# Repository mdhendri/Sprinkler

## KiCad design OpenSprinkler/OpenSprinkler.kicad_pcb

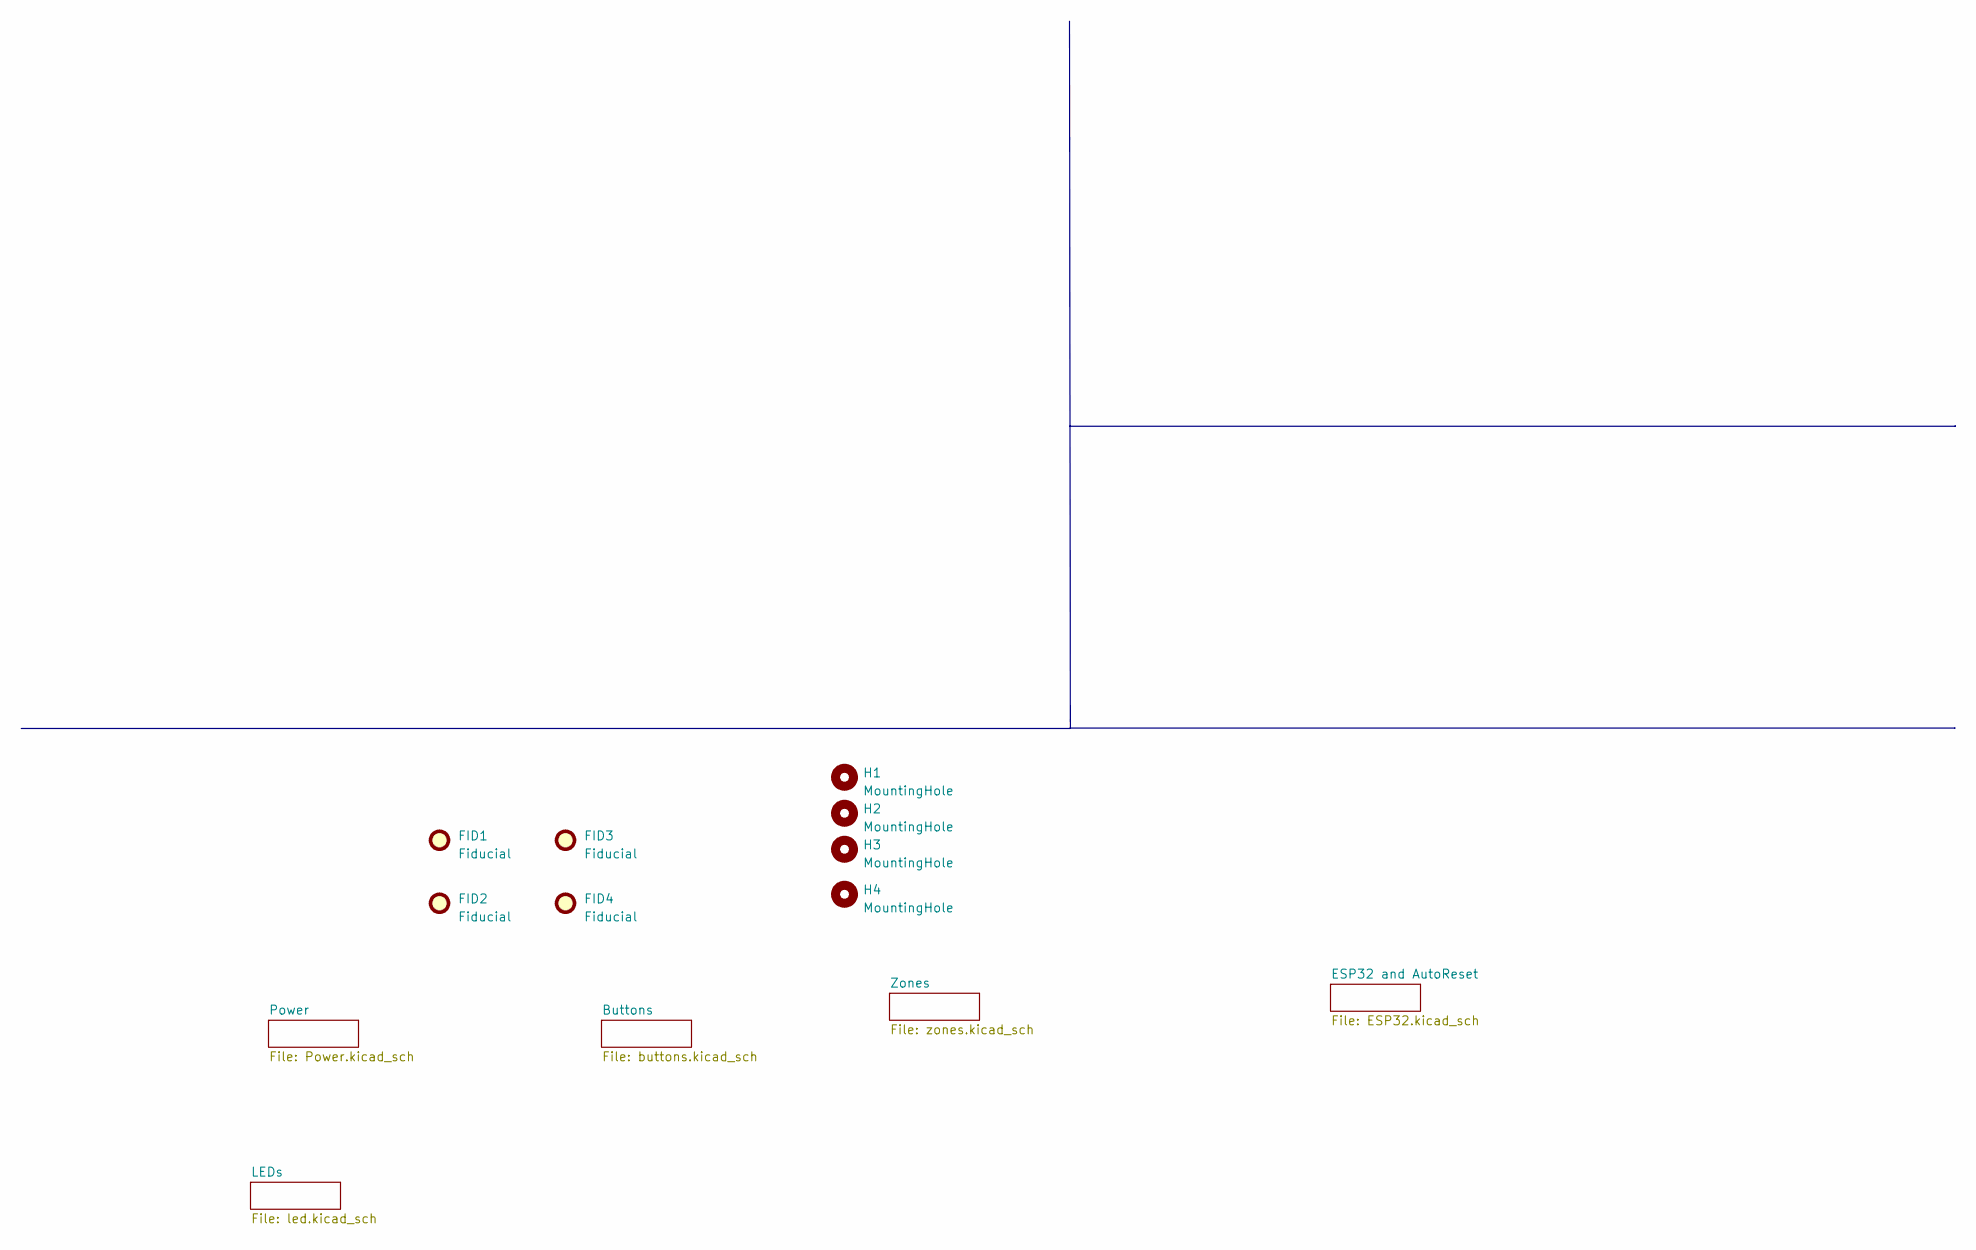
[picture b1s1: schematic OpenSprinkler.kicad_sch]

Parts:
FID1, FID2, FID3, FID4: Fiducial; Fiducial_0.5mm_Mask1.5mm
H1, H2, H3, H4: MountingHole; MountingHole_2.7mm

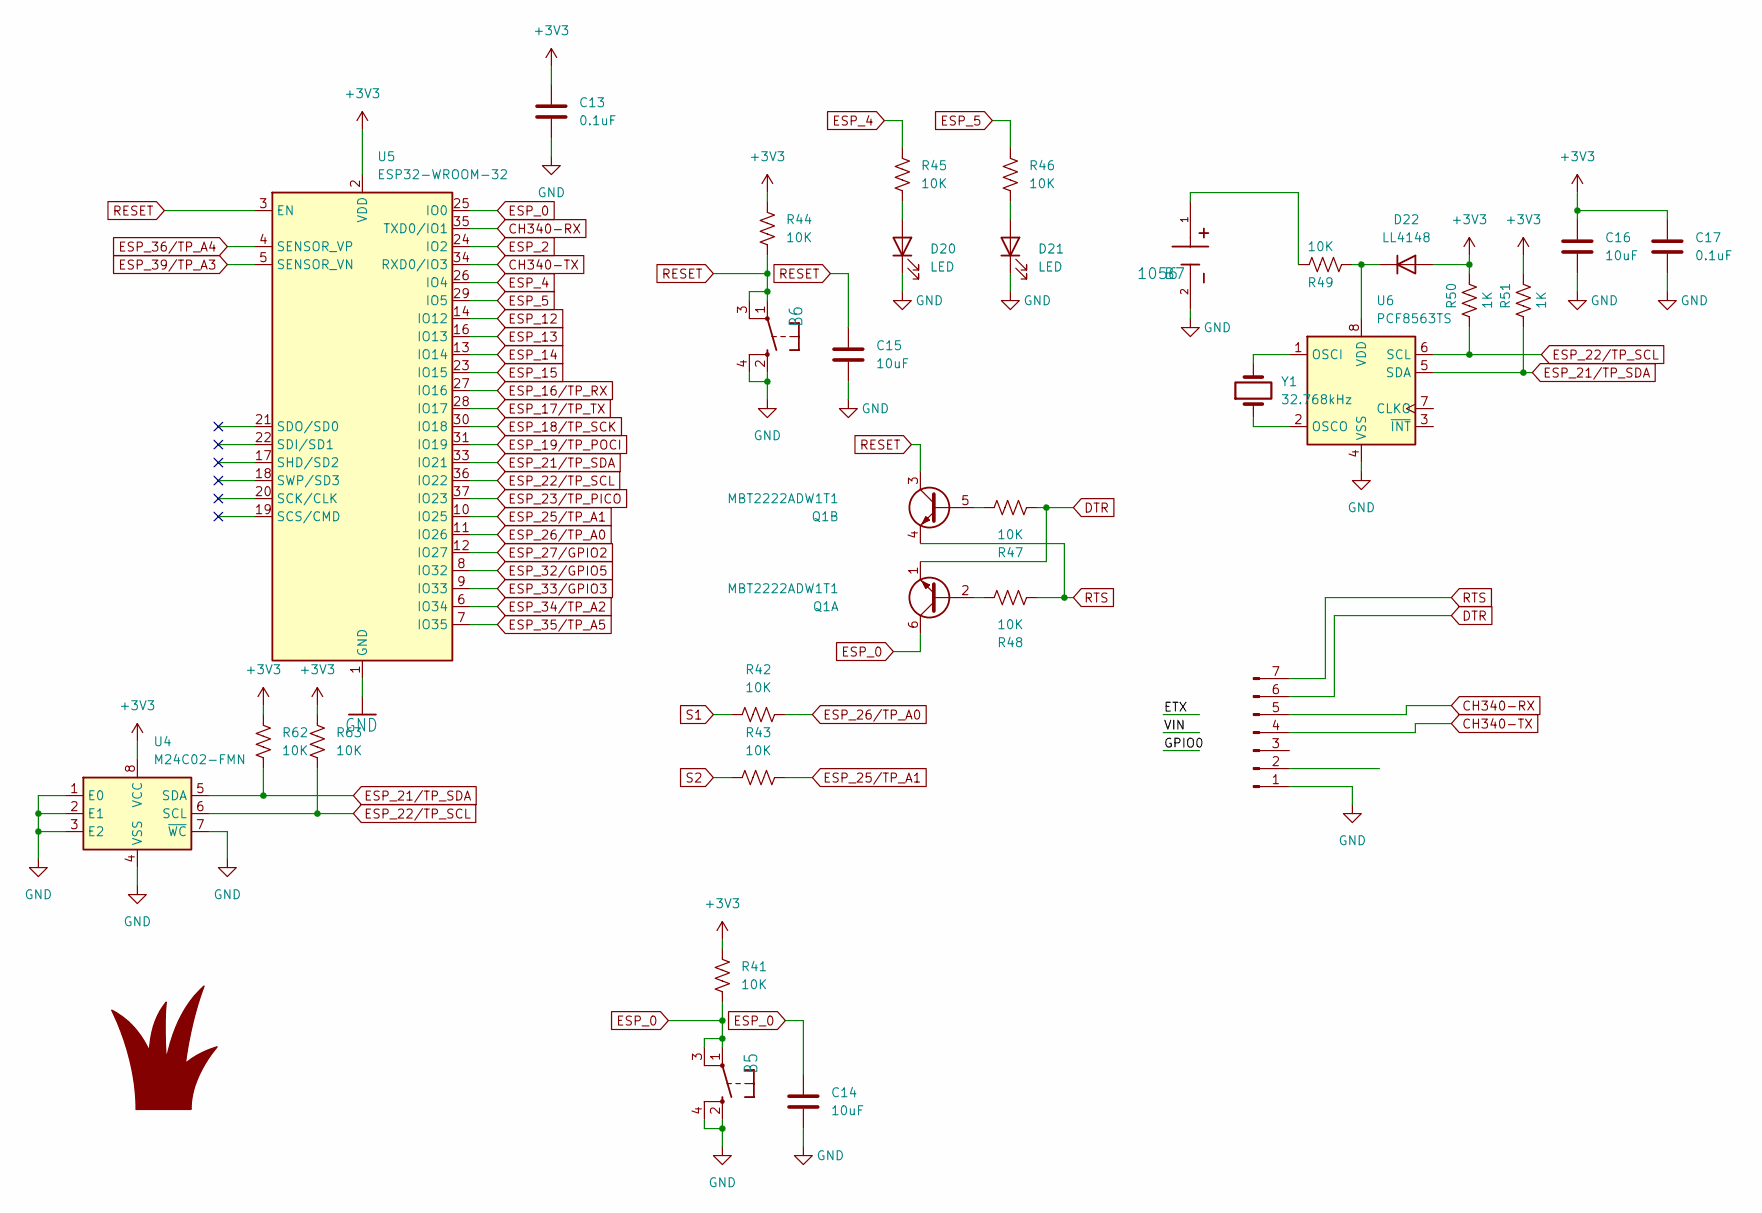
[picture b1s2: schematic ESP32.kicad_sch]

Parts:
B5, B6: SPST_TACTEVQQ2; SW_SPST_EVQQ2
B7: 1056; 1048P_KEY; PARTREV C
C13, C17: 0.1uF; C_0603_1608Metric_Pad1.08x0.95mm_HandSolder
C14, C15, C16: 10uF; C_0603_1608Metric_Pad1.08x0.95mm_HandSolder
D20, D21: LED; LED_0603_1608Metric_Pad1.05x0.95mm_HandSolder
D22: LL4148; D_MiniMELF
Q1: MBT2222ADW1T1; SOT-363_SC-70-6
R41, R42, R43, R44, R45, R46, R47, R48, R49, R62, R63: 10K; R_0603_1608Metric_Pad0.98x0.95mm_HandSolder
R50, R51: 1K; R_0603_1608Metric_Pad0.98x0.95mm_HandSolder
U4: M24C02-FMN; SOIC-8_3.9x4.9mm_P1.27mm
U5: ESP32-WROOM-32
U6: PCF8563TS; MSOP-8_3x3mm_P0.65mm
U$1: GOLDFINGER_2X3; PinHeader_1x07_P2.54mm_Vertical
Y1: 32.768kHz; XTAL_ECS-31B_ECS

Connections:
+3V3: C13.1, C16.1, C17.1, D22.2 (A), R41.1, R44.1, R50.1, R51.1, R62.1, R63.1, U4.8 (VCC), U5.2 (VDD); also elsewhere on the board
CH340-RX: U5.35 (TXD0/IO1), U$1.5
CH340-TX: U5.34 (RXD0/IO3), U$1.4
DTR: Q1.1 (E1), R47.1, U$1.6
ESP_0: B5.1, B5.3, C14.1, Q1.6 (C1), R41.2, U5.25 (IO0)
ESP_2: U5.24 (IO2)
ESP_4: R45.1, U5.26 (IO4)
ESP_5: R46.1, U5.29 (IO5)
ESP_12: U5.14 (IO12); also elsewhere on the board
ESP_13: U5.16 (IO13); also elsewhere on the board
ESP_14: U5.13 (IO14); also elsewhere on the board
ESP_15: U5.23 (IO15); also elsewhere on the board
ESP_16/TP_RX: U5.27 (IO16)
ESP_17/TP_TX: U5.28 (IO17)
ESP_18/TP_SCK: U5.30 (IO18)
ESP_19/TP_POCI: U5.31 (IO19)
ESP_21/TP_SDA: R51.2, R62.2, U4.5 (SDA), U5.33 (IO21), U6.5 (SDA); also elsewhere on the board
ESP_22/TP_SCL: R50.2, R63.2, U4.6 (SCL), U5.36 (IO22), U6.6 (SCL); also elsewhere on the board
ESP_23/TP_PICO: U5.37 (IO23)
ESP_25/TP_A1: R43.2, U5.10 (IO25)
ESP_26/TP_A0: R42.2, U5.11 (IO26)
ESP_27/GPIO2: U5.12 (IO27); also elsewhere on the board
ESP_32/GPIO5: U5.8 (IO32)
ESP_33/GPIO3: U5.9 (IO33)
ESP_34/TP_A2: U5.6 (IO34); also elsewhere on the board
ESP_35/TP_A5: U5.7 (IO35)
ESP_36/TP_A4: U5.4 (SENSOR_VP)
ESP_39/TP_A3: U5.5 (SENSOR_VN)
GND: B5.2, B5.4, B6.2, B6.4, B7.2, C13.2, C14.2, C15.2, C16.2, C17.2, D20.1 (K), D21.1 (K), U4.1 (E0), U4.2 (E1), U4.3 (E2), U4.4 (VSS), U4.7 (~WC), U5.1 (GND), U5.15 (GND), U5.38 (GND), U5.39 (GND), U6.4 (VSS), U$1.1; also elsewhere on the board
unnamed: B7.1, R49.1
unnamed: D20.2 (A), R45.2
unnamed: D21.2 (A), R46.2
unnamed: D22.1 (K), R49.2, U6.8 (VDD)
unnamed: Q1.2 (B1), R48.2
unnamed: Q1.5 (B2), R47.2
unnamed: U6.1 (OSCI), Y1.2
unnamed: U6.2 (OSCO), Y1.1
RESET: B6.1, B6.3, C15.1, Q1.3 (C2), R44.2, U5.3 (EN)
RTS: Q1.4 (E2), R48.1, U$1.7
S1: R42.1; also elsewhere on the board
S2: R43.1; also elsewhere on the board

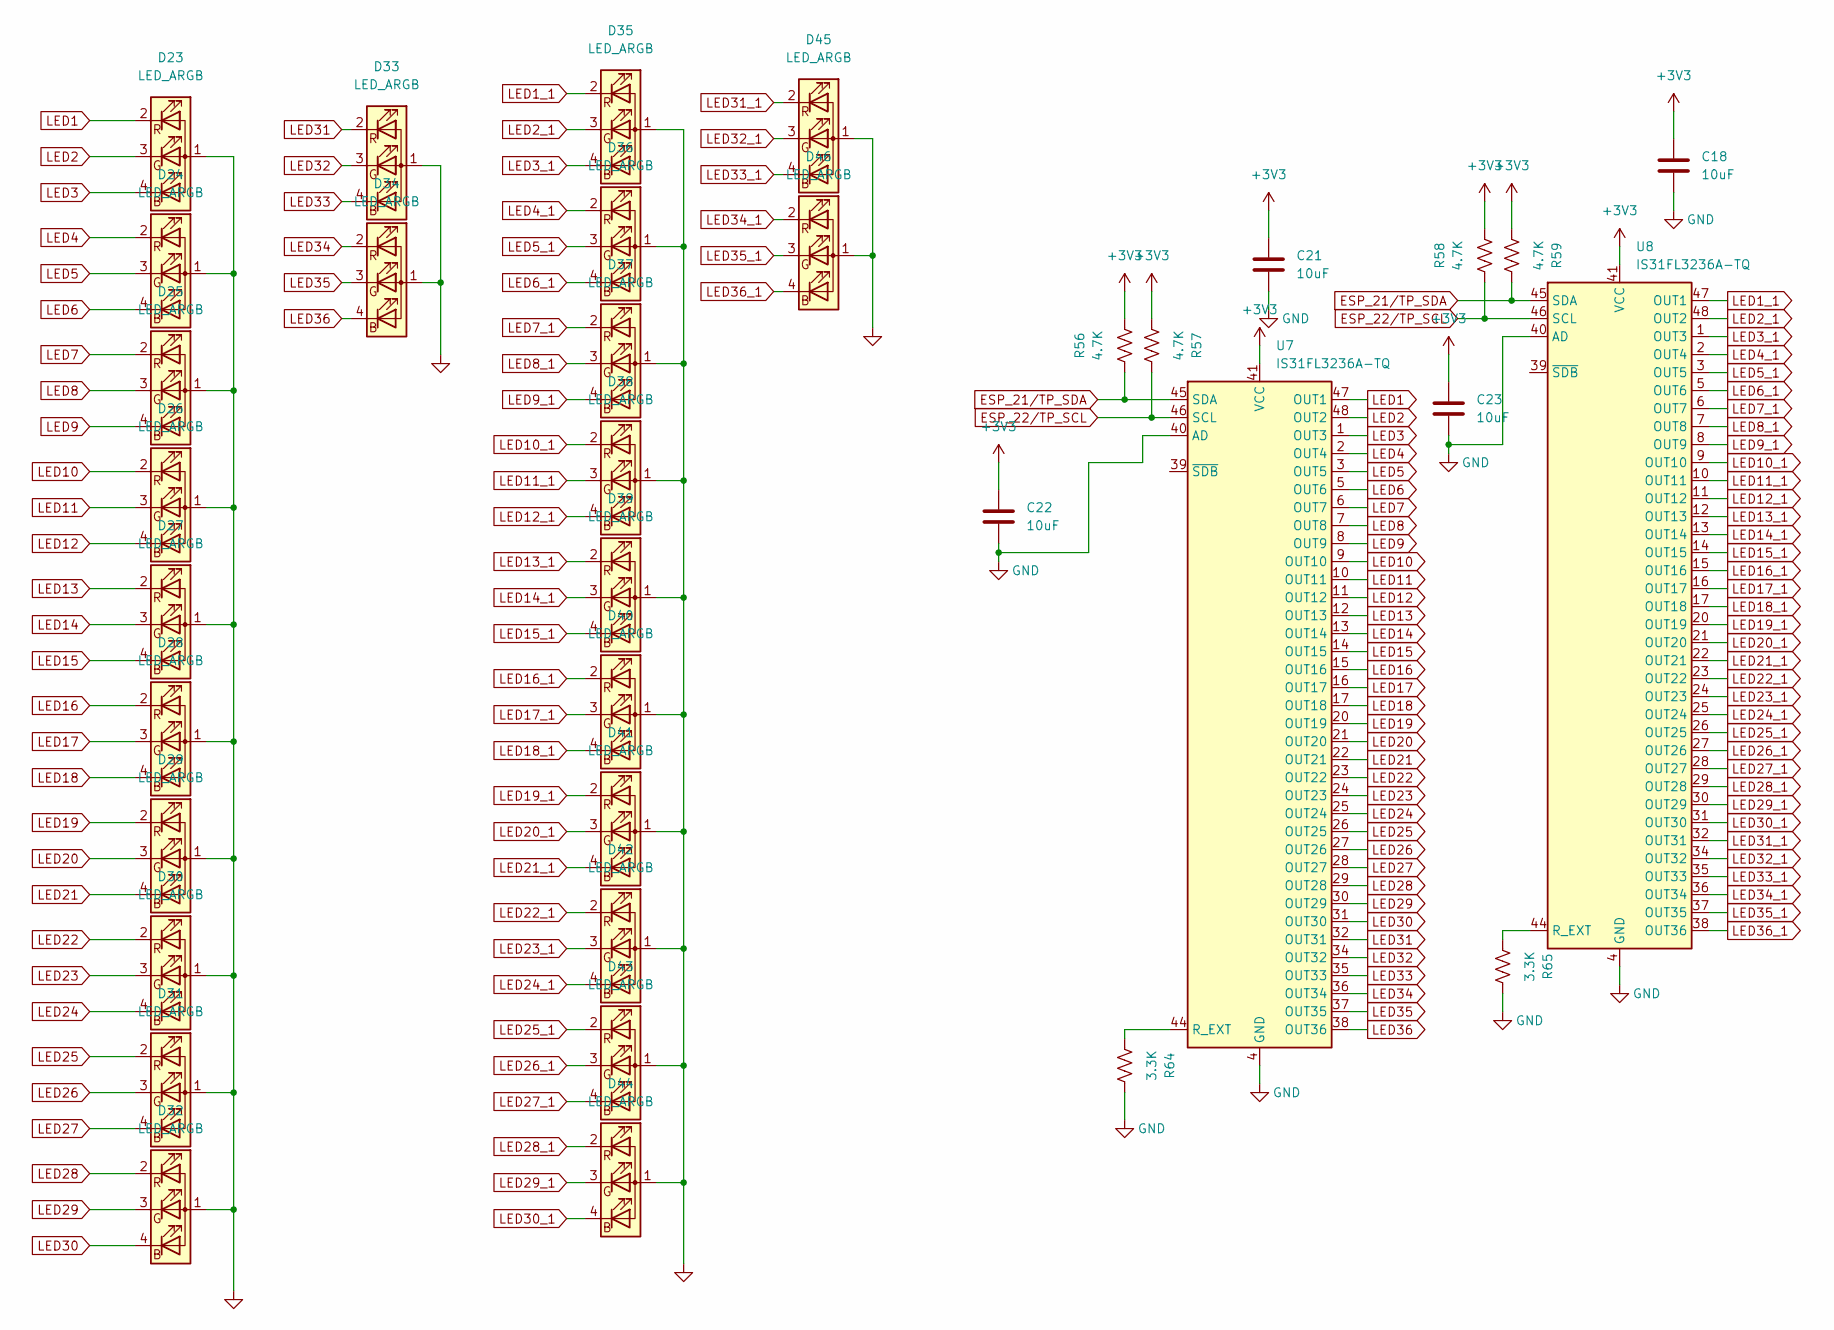
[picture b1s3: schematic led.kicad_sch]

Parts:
C18, C21, C22, C23: 10uF; C_0603_1608Metric_Pad1.08x0.95mm_HandSolder
D23, D24, D25, D26, D27, D28, D29, D30, D31, D32, D33, D34, D35, D36, D37, D38, D39, D40, D41, D42, D43, D44, D45, D46: LED_ARGB; LED_EASR3212RGBA0
R56, R57, R58, R59: 4.7K; R_0603_1608Metric_Pad0.98x0.95mm_HandSolder
R64, R65: 3.3K; R_0603_1608Metric_Pad0.98x0.95mm_HandSolder
U7, U8: IS31FL3236A-TQ; TQFP-48-1EP_7x7mm_P0.5mm_EP4.11x4.11mm

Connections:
+3V3: C18.1, C21.1, C22.1, C23.1, R56.2, R57.1, R58.2, R59.1, U7.41 (VCC), U8.41 (VCC); also elsewhere on the board
ESP_21/TP_SDA: R56.1, R59.2, U7.45 (SDA), U8.45 (SDA); also elsewhere on the board
ESP_22/TP_SCL: R57.2, R58.1, U7.46 (SCL), U8.46 (SCL); also elsewhere on the board
GND: C18.2, C21.2, C22.2, C23.2, D23.1 (A), D24.1 (A), D25.1 (A), D26.1 (A), D27.1 (A), D28.1 (A), D29.1 (A), D30.1 (A), D31.1 (A), D32.1 (A), D33.1 (A), D34.1 (A), D35.1 (A), D36.1 (A), D37.1 (A), D38.1 (A), D39.1 (A), D40.1 (A), D41.1 (A), D42.1 (A), D43.1 (A), D44.1 (A), D45.1 (A), D46.1 (A), R64.2, R65.2, U7.4 (GND), U7.18 (GND), U7.19 (GND), U7.33 (GND), U7.40 (AD), U7.42 (GND), U7.43 (GND), U7.49 (GND), U8.4 (GND), U8.18 (GND), U8.19 (GND), U8.33 (GND), U8.40 (AD), U8.42 (GND), U8.43 (GND), U8.49 (GND); also elsewhere on the board
LED1: D23.2 (RK), U7.47 (OUT1)
LED1_1: D35.2 (RK), U8.47 (OUT1)
LED2: D23.3 (GK), U7.48 (OUT2)
LED2_1: D35.3 (GK), U8.48 (OUT2)
LED3: D23.4 (BK), U7.1 (OUT3)
LED3_1: D35.4 (BK), U8.1 (OUT3)
LED4: D24.2 (RK), U7.2 (OUT4)
LED4_1: D36.2 (RK), U8.2 (OUT4)
LED5: D24.3 (GK), U7.3 (OUT5)
LED5_1: D36.3 (GK), U8.3 (OUT5)
LED6: D24.4 (BK), U7.5 (OUT6)
LED6_1: D36.4 (BK), U8.5 (OUT6)
LED7: D25.2 (RK), U7.6 (OUT7)
LED7_1: D37.2 (RK), U8.6 (OUT7)
LED8: D25.3 (GK), U7.7 (OUT8)
LED8_1: D37.3 (GK), U8.7 (OUT8)
LED9: D25.4 (BK), U7.8 (OUT9)
LED9_1: D37.4 (BK), U8.8 (OUT9)
LED10: D26.2 (RK), U7.9 (OUT10)
LED10_1: D38.2 (RK), U8.9 (OUT10)
LED11: D26.3 (GK), U7.10 (OUT11)
LED11_1: D38.3 (GK), U8.10 (OUT11)
LED12: D26.4 (BK), U7.11 (OUT12)
LED12_1: D38.4 (BK), U8.11 (OUT12)
LED13: D27.2 (RK), U7.12 (OUT13)
LED13_1: D39.2 (RK), U8.12 (OUT13)
LED14: D27.3 (GK), U7.13 (OUT14)
LED14_1: D39.3 (GK), U8.13 (OUT14)
LED15: D27.4 (BK), U7.14 (OUT15)
LED15_1: D39.4 (BK), U8.14 (OUT15)
LED16: D28.2 (RK), U7.15 (OUT16)
LED16_1: D40.2 (RK), U8.15 (OUT16)
LED17: D28.3 (GK), U7.16 (OUT17)
LED17_1: D40.3 (GK), U8.16 (OUT17)
LED18: D28.4 (BK), U7.17 (OUT18)
LED18_1: D40.4 (BK), U8.17 (OUT18)
LED19: D29.2 (RK), U7.20 (OUT19)
LED19_1: D41.2 (RK), U8.20 (OUT19)
LED20: D29.3 (GK), U7.21 (OUT20)
LED20_1: D41.3 (GK), U8.21 (OUT20)
LED21: D29.4 (BK), U7.22 (OUT21)
LED21_1: D41.4 (BK), U8.22 (OUT21)
LED22: D30.2 (RK), U7.23 (OUT22)
LED22_1: D42.2 (RK), U8.23 (OUT22)
LED23: D30.3 (GK), U7.24 (OUT23)
LED23_1: D42.3 (GK), U8.24 (OUT23)
LED24: D30.4 (BK), U7.25 (OUT24)
LED24_1: D42.4 (BK), U8.25 (OUT24)
LED25: D31.2 (RK), U7.26 (OUT25)
LED25_1: D43.2 (RK), U8.26 (OUT25)
LED26: D31.3 (GK), U7.27 (OUT26)
LED26_1: D43.3 (GK), U8.27 (OUT26)
LED27: D31.4 (BK), U7.28 (OUT27)
LED27_1: D43.4 (BK), U8.28 (OUT27)
LED28: D32.2 (RK), U7.29 (OUT28)
LED28_1: D44.2 (RK), U8.29 (OUT28)
LED29: D32.3 (GK), U7.30 (OUT29)
LED29_1: D44.3 (GK), U8.30 (OUT29)
LED30: D32.4 (BK), U7.31 (OUT30)
LED30_1: D44.4 (BK), U8.31 (OUT30)
LED31: D33.2 (RK), U7.32 (OUT31)
LED31_1: D45.2 (RK), U8.32 (OUT31)
LED32: D33.3 (GK), U7.34 (OUT32)
LED32_1: D45.3 (GK), U8.34 (OUT32)
LED33: D33.4 (BK), U7.35 (OUT33)
LED33_1: D45.4 (BK), U8.35 (OUT33)
LED34: D34.2 (RK), U7.36 (OUT34)
LED34_1: D46.2 (RK), U8.36 (OUT34)
LED35: D34.3 (GK), U7.37 (OUT35)
LED35_1: D46.3 (GK), U8.37 (OUT35)
LED36: D34.4 (BK), U7.38 (OUT36)
LED36_1: D46.4 (BK), U8.38 (OUT36)
unnamed: R64.1, U7.44 (R_EXT)
unnamed: R65.1, U8.44 (R_EXT)

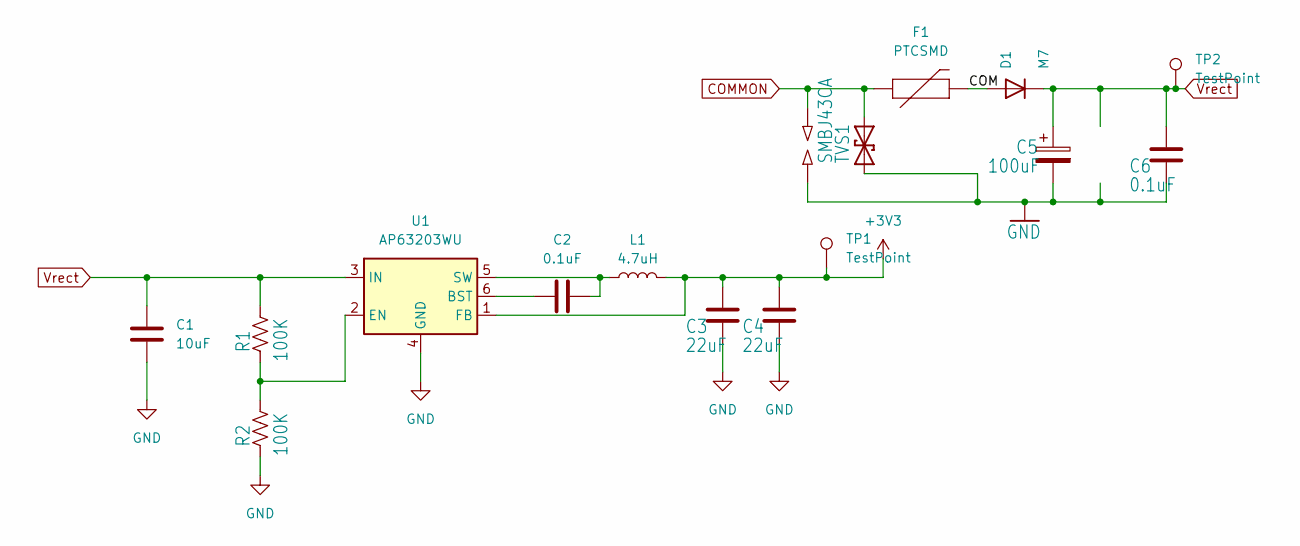
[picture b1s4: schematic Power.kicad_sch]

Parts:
C1: 10uF; C_1210_3225Metric_Pad1.33x2.70mm_HandSolder
C2: 0.1uF; C_0805_2012Metric_Pad1.18x1.45mm_HandSolder
C3, C4: 22uF; C_0805_2012Metric_Pad1.18x1.45mm_HandSolder
C5: 100uF; C_Elec_8x10.2
C6: 0.1uF; C_1206_3216Metric_Pad1.33x1.80mm_HandSolder
D1: M7; D_SMA
F1: PTCSMD; Fuse_Bourns_MF-SM_7.98x5.44mm
L1: 4.7uH; L_Abracon_ASPI-0425
R1, R2: 100K; R_0603_1608Metric_Pad0.98x0.95mm_HandSolder
SP1: PCB-SGAP; Sparkgap
TP1, TP2: TestPoint; TestPoint_Pad_D1.0mm
TVS1: SMBJ43CA; SMBJSeries_LTF
U1: AP63203WU; TSOT-23-6

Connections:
+3V3: C3.1, C4.1, L1.2, TP1.1, U1.1 (FB); also elsewhere on the board
/Power/COM: D1.2 (A), F1.2
COMMON: F1.1, SP1.2, TVS1.2 (C); also elsewhere on the board
GND: C1.2, C3.2, C4.2, C5.2, C6.2, R2.1, SP1.1, TVS1.1 (A), U1.4 (GND); also elsewhere on the board
unnamed: C2.1, U1.6 (BST)
unnamed: R1.1, R2.2, U1.2 (EN)
unnamed: C2.2, L1.1, U1.5 (SW)
Vrect: C1.1, C5.1, C6.1, D1.1 (K), R1.2, TP2.1, U1.3 (IN)

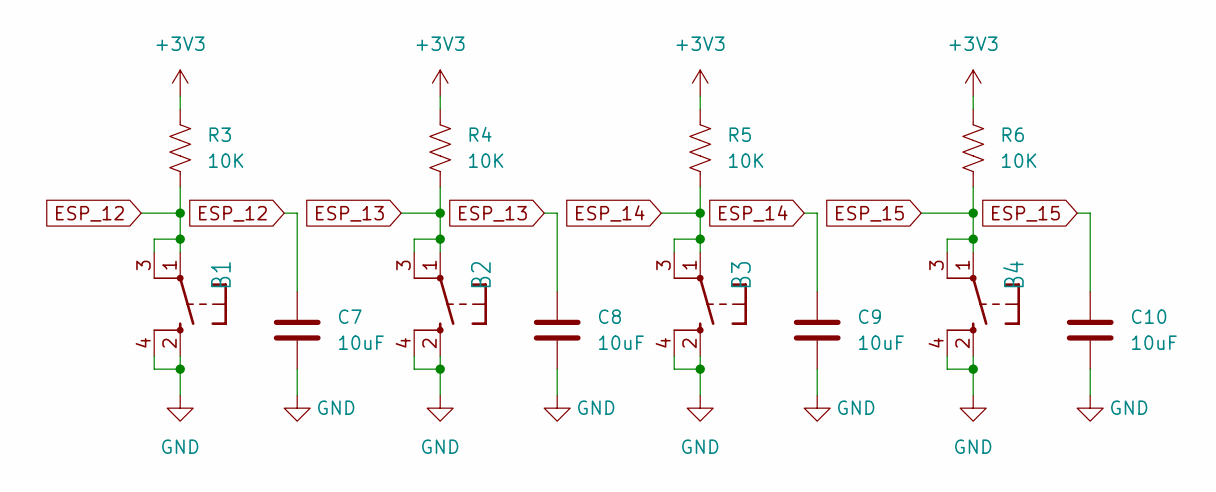
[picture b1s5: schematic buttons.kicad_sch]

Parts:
B1, B2, B3, B4: SPST_TACTEVQQ2; SW_SPST_EVQQ2
C7, C8, C9, C10: 10uF; C_0603_1608Metric_Pad1.08x0.95mm_HandSolder
R3, R4, R5, R6: 10K; R_0603_1608Metric_Pad0.98x0.95mm_HandSolder

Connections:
+3V3: R3.1, R4.1, R5.1, R6.1; also elsewhere on the board
ESP_12: B1.1, B1.3, C7.1, R3.2; also elsewhere on the board
ESP_13: B2.1, B2.3, C8.1, R4.2; also elsewhere on the board
ESP_14: B3.1, B3.3, C9.1, R5.2; also elsewhere on the board
ESP_15: B4.1, B4.3, C10.1, R6.2; also elsewhere on the board
GND: B1.2, B1.4, B2.2, B2.4, B3.2, B3.4, B4.2, B4.4, C7.2, C8.2, C9.2, C10.2; also elsewhere on the board

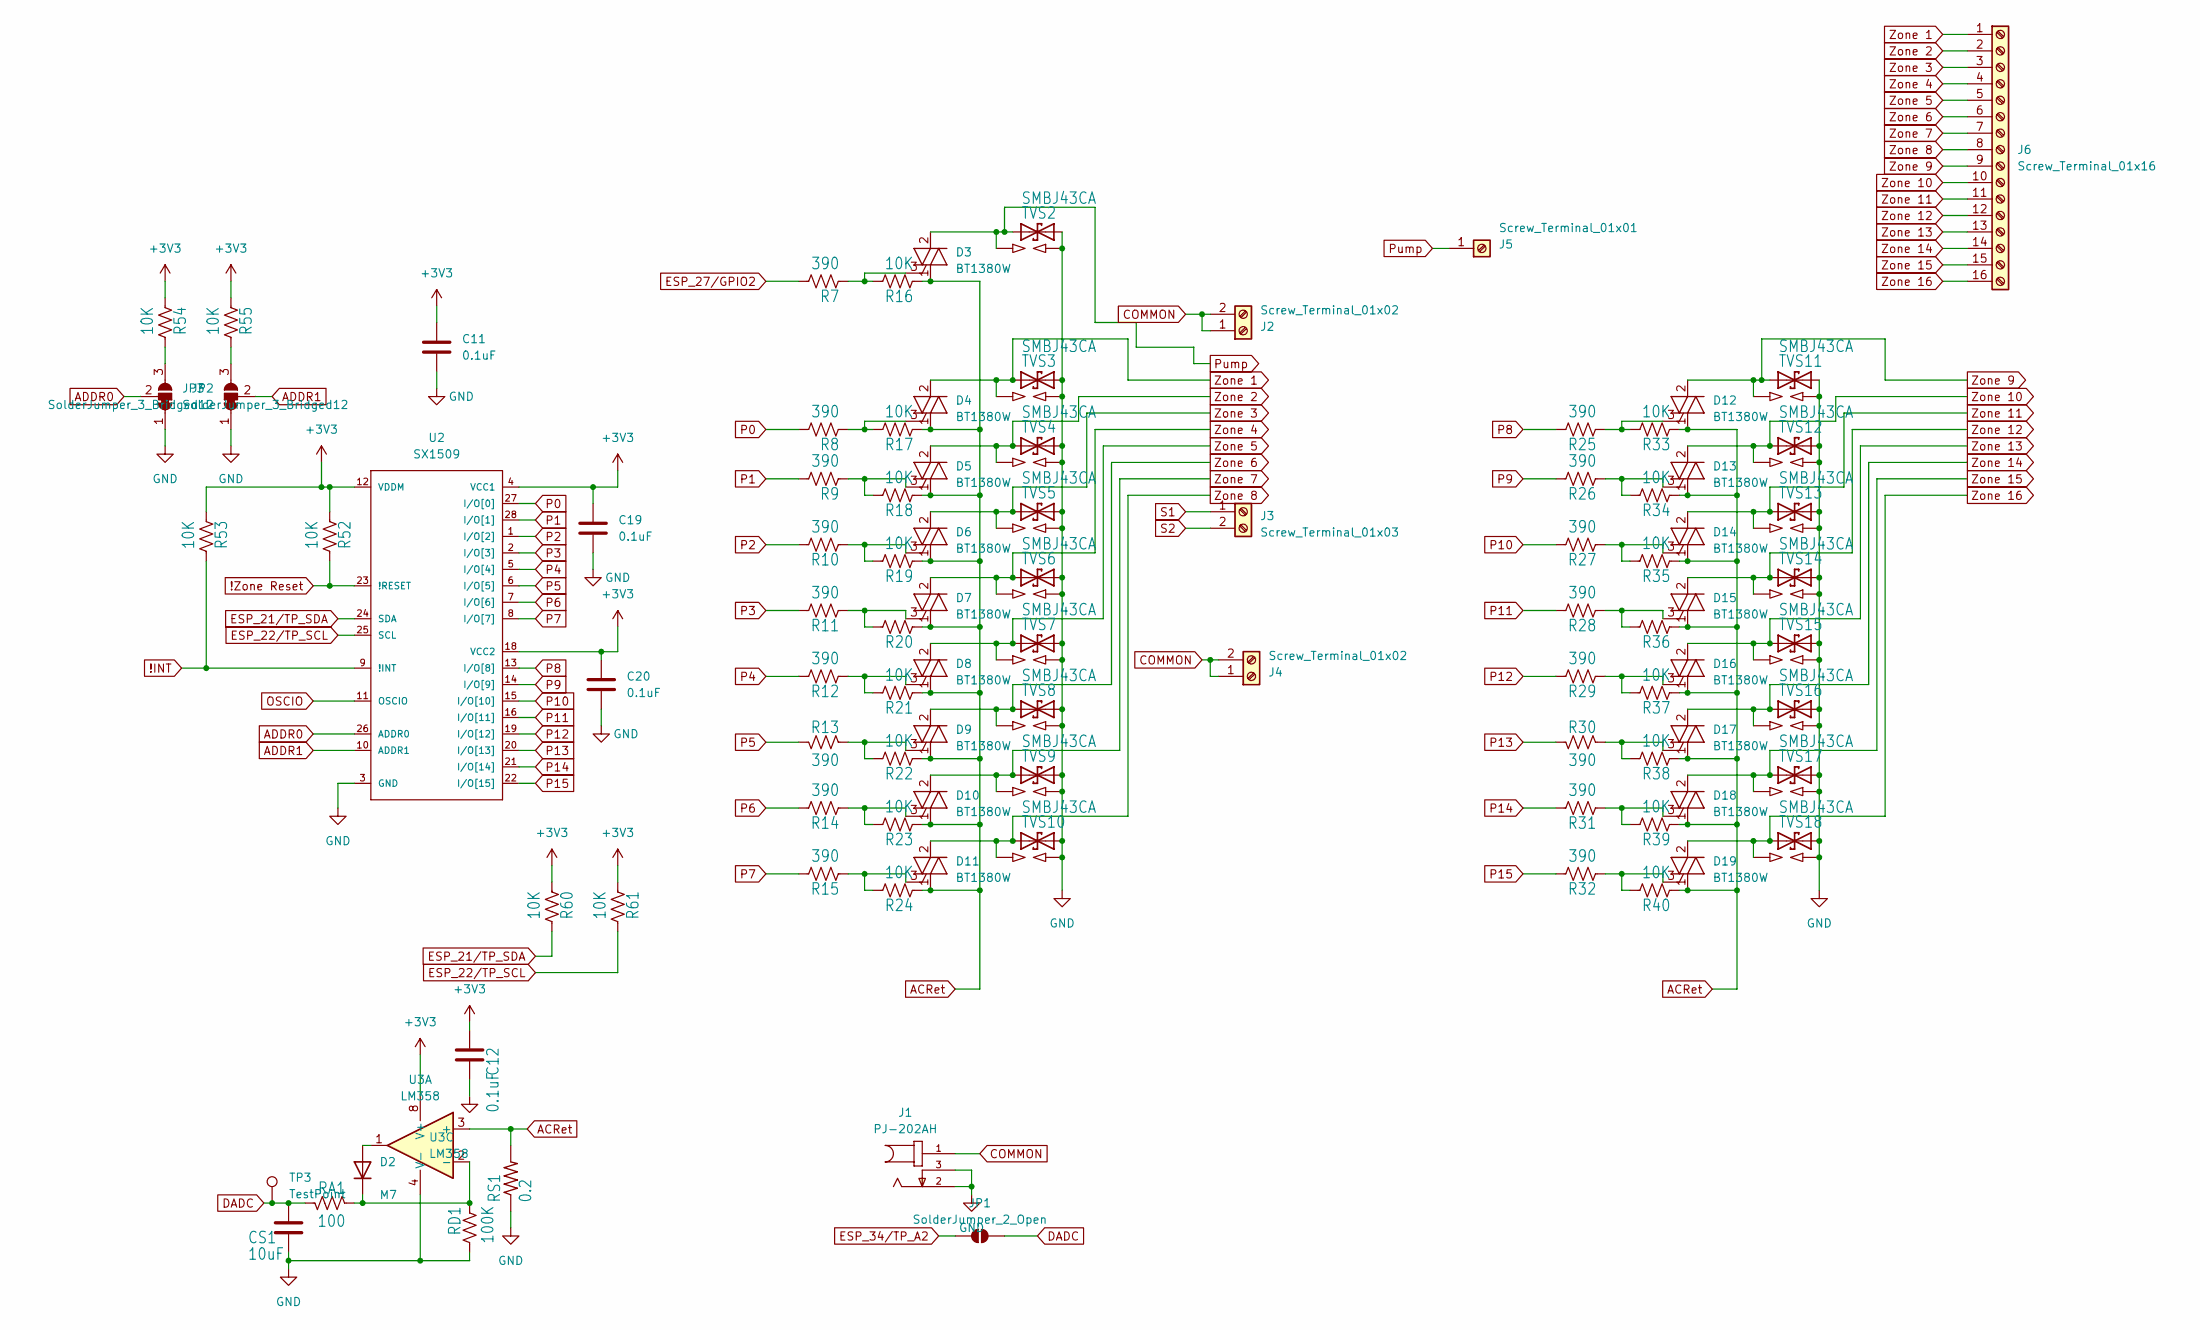
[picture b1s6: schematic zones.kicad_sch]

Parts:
C11, C12, C19, C20: 0.1uF; C_0603_1608Metric_Pad1.08x0.95mm_HandSolder
CS1: 10uF; C_0603_1608Metric_Pad1.08x0.95mm_HandSolder
D2: M7; D_SMA
D3, D4, D5, D6, D7, D8, D9, D10, D11, D12, D13, D14, D15, D16, D17, D18, D19: BT1380W; SOT-223
J1: PJ-202AH; BarrelJack_Kycon_KLDX-0202-xC_Horizontal; PART_REV 1.02
J2, J4: Screw_Terminal_01x02; TerminalBlock_WAGO_236-502_1x02_P7.50mm_45Degree
J3: Screw_Terminal_01x03; TerminalBlock_WAGO_236-502_1x02_P7.50mm_45Degree
J5: Screw_Terminal_01x01; TerminalBlock_WAGO_236-501_1x01_P7.50mm_45Degree
J6: Screw_Terminal_01x16; TerminalBlock_WAGO_236-516_1x16_P7.50mm_45Degree
JP1: SolderJumper_2_Open; SolderJumper-2_P1.3mm_Open_Pad1.0x1.5mm
JP2, JP3: SolderJumper_3_Bridged12; SolderJumper-3_P1.3mm_Bridged2Bar12_Pad1.0x1.5mm
R7, R8, R9, R10, R11, R12, R13, R14, R15, R25, R26, R27, R28, R29, R30, R31, R32: 390; R_0603_1608Metric_Pad0.98x0.95mm_HandSolder
R16, R17, R18, R19, R20, R21, R22, R23, R24, R33, R34, R35, R36, R37, R38, R39, R40, R52, R53, R54, R55, R60, R61: 10K; R_0603_1608Metric_Pad0.98x0.95mm_HandSolder
RA1: 100; R_0603_1608Metric_Pad0.98x0.95mm_HandSolder
RD1: 100K; R_0603_1608Metric_Pad0.98x0.95mm_HandSolder
RS1: 0.2; R_1206_3216Metric_Pad1.30x1.75mm_HandSolder
SP2, SP3, SP4, SP5, SP6, SP7, SP8, SP9, SP10, SP11, SP12, SP13, SP14, SP15, SP16, SP17, SP18: PCB-SGAP; Sparkgap
TP3: TestPoint; TestPoint_Pad_D1.0mm
TVS2, TVS3, TVS4, TVS5, TVS6, TVS7, TVS8, TVS9, TVS10, TVS11, TVS12, TVS13, TVS14, TVS15, TVS16, TVS17, TVS18: SMBJ43CA; D_SMB
U2: SX1509; QFN40P400X400X60-29N
U3: LM358; SOIC-8_3.9x4.9mm_P1.27mm

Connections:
!INT: R53.2, U2.9 (!INT)
!Zone Reset: R52.2, U2.23 (!RESET)
+3V3: C11.1, C12.1, C19.1, C20.1, R52.1, R53.1, R54.1, R55.1, R60.1, R61.1, U2.4 (VCC1), U2.12 (VDDM), U2.18 (VCC2), U3.8 (V+); also elsewhere on the board
ACRet: D3.1 (A1), D4.1 (A1), D5.1 (A1), D6.1 (A1), D7.1 (A1), D8.1 (A1), D9.1 (A1), D10.1 (A1), D11.1 (A1), D12.1 (A1), D13.1 (A1), D14.1 (A1), D15.1 (A1), D16.1 (A1), D17.1 (A1), D18.1 (A1), D19.1 (A1), R16.1, R17.1, R18.1, R19.1, R20.1, R21.1, R22.1, R23.1, R24.1, R33.1, R34.1, R35.1, R36.1, R37.1, R38.1, R39.1, R40.1, RS1.2, U3.3 (+)
ADDR0: JP3.2 (C), U2.26 (ADDR0)
ADDR1: JP2.2 (C), U2.10 (ADDR1)
COMMON: J1.1, J2.1, J2.2, J4.1, J4.2; also elsewhere on the board
DADC: CS1.1, JP1.2 (B), RA1.2, TP3.1
ESP_21/TP_SDA: R60.2, U2.24 (SDA); also elsewhere on the board
ESP_22/TP_SCL: R61.2, U2.25 (SCL); also elsewhere on the board
ESP_27/GPIO2: R7.2; also elsewhere on the board
ESP_34/TP_A2: JP1.1 (A); also elsewhere on the board
GND: C11.2, C12.2, C19.2, C20.2, CS1.2, J1.2, J1.3, JP2.1 (A), JP3.1 (A), RD1.1, RS1.1, SP2.2, SP3.2, SP4.2, SP5.2, SP6.2, SP7.2, SP8.2, SP9.2, SP10.2, SP11.2, SP12.2, SP13.2, SP14.2, SP15.2, SP16.2, SP17.2, SP18.2, TVS2.2 (C), TVS3.2 (C), TVS4.2 (C), TVS5.2 (C), TVS6.2 (C), TVS7.2 (C), TVS8.2 (C), TVS9.2 (C), TVS10.2 (C), TVS11.2 (C), TVS12.2 (C), TVS13.2 (C), TVS14.2 (C), TVS15.2 (C), TVS16.2 (C), TVS17.2 (C), TVS18.2 (C), U2.3 (GND), U2.17 (GND), U2.29 (GND), U3.4 (V-); also elsewhere on the board
unnamed: D2.2 (A), U3.1
unnamed: D2.1 (K), RA1.1, RD1.2, U3.2 (-)
unnamed: D3.3 (G), R7.1, R16.2
unnamed: D4.3 (G), R8.1, R17.2
unnamed: D5.3 (G), R9.1, R18.2
unnamed: D6.3 (G), R10.1, R19.2
unnamed: D7.3 (G), R11.1, R20.2
unnamed: D8.3 (G), R12.1, R21.2
unnamed: D9.3 (G), R13.1, R22.2
unnamed: D10.3 (G), R14.1, R23.2
unnamed: D11.3 (G), R15.1, R24.2
unnamed: D12.3 (G), R25.1, R33.2
unnamed: D13.3 (G), R26.1, R34.2
unnamed: D14.3 (G), R27.1, R35.2
unnamed: D15.3 (G), R28.1, R36.2
unnamed: D16.3 (G), R29.1, R37.2
unnamed: D17.3 (G), R30.1, R38.2
unnamed: D18.3 (G), R31.1, R39.2
unnamed: D19.3 (G), R32.1, R40.2
unnamed: JP2.3 (B), R55.2
unnamed: JP3.3 (B), R54.2
OSCIO: U2.11 (OSCIO)
P0: R8.2, U2.27 (I/O[0])
P1: R9.2, U2.28 (I/O[1])
P2: R10.2, U2.1 (I/O[2])
P3: R11.2, U2.2 (I/O[3])
P4: R12.2, U2.5 (I/O[4])
P5: R13.2, U2.6 (I/O[5])
P6: R14.2, U2.7 (I/O[6])
P7: R15.2, U2.8 (I/O[7])
P8: R25.2, U2.13 (I/O[8])
P9: R26.2, U2.14 (I/O[9])
P10: R27.2, U2.15 (I/O[10])
P11: R28.2, U2.16 (I/O[11])
P12: R29.2, U2.19 (I/O[12])
P13: R30.2, U2.20 (I/O[13])
P14: R31.2, U2.21 (I/O[14])
P15: R32.2, U2.22 (I/O[15])
Pump: D3.2 (A2), D3.4 (A4), J5.1, SP2.1, TVS2.1 (A)
S1: J3.1; also elsewhere on the board
S2: J3.2; also elsewhere on the board
Zone 1: D4.2 (A2), D4.4 (A4), J6.1, SP3.1, TVS3.1 (A)
Zone 2: D5.2 (A2), D5.4 (A4), J6.2, SP4.1, TVS4.1 (A)
Zone 3: D6.2 (A2), D6.4 (A4), J6.3, SP5.1, TVS5.1 (A)
Zone 4: D7.2 (A2), D7.4 (A4), J6.4, SP6.1, TVS6.1 (A)
Zone 5: D8.2 (A2), D8.4 (A4), J6.5, SP7.1, TVS7.1 (A)
Zone 6: D9.2 (A2), D9.4 (A4), J6.6, SP8.1, TVS8.1 (A)
Zone 7: D10.2 (A2), D10.4 (A4), J6.7, SP9.1, TVS9.1 (A)
Zone 8: D11.2 (A2), D11.4 (A4), J6.8, SP10.1, TVS10.1 (A)
Zone 9: D12.2 (A2), D12.4 (A4), J6.9, SP11.1, TVS11.1 (A)
Zone 10: D13.2 (A2), D13.4 (A4), J6.10, SP12.1, TVS12.1 (A)
Zone 11: D14.2 (A2), D14.4 (A4), J6.11, SP13.1, TVS13.1 (A)
Zone 12: D15.2 (A2), D15.4 (A4), J6.12, SP14.1, TVS14.1 (A)
Zone 13: D16.2 (A2), D16.4 (A4), J6.13, SP15.1, TVS15.1 (A)
Zone 14: D17.2 (A2), D17.4 (A4), J6.14, SP16.1, TVS16.1 (A)
Zone 15: D18.2 (A2), D18.4 (A4), J6.15, SP17.1, TVS17.1 (A)
Zone 16: D19.2 (A2), D19.4 (A4), J6.16, SP18.1, TVS18.1 (A)

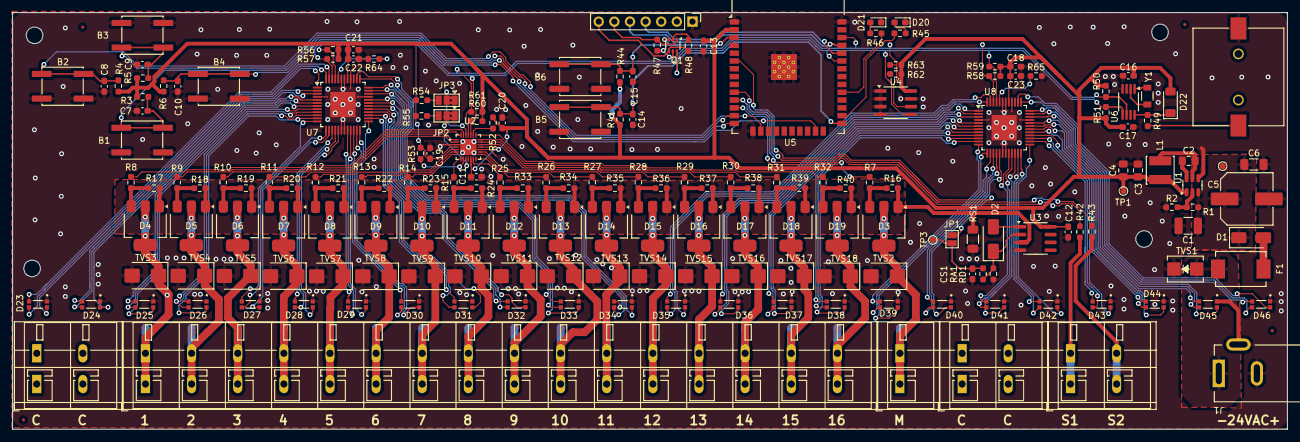
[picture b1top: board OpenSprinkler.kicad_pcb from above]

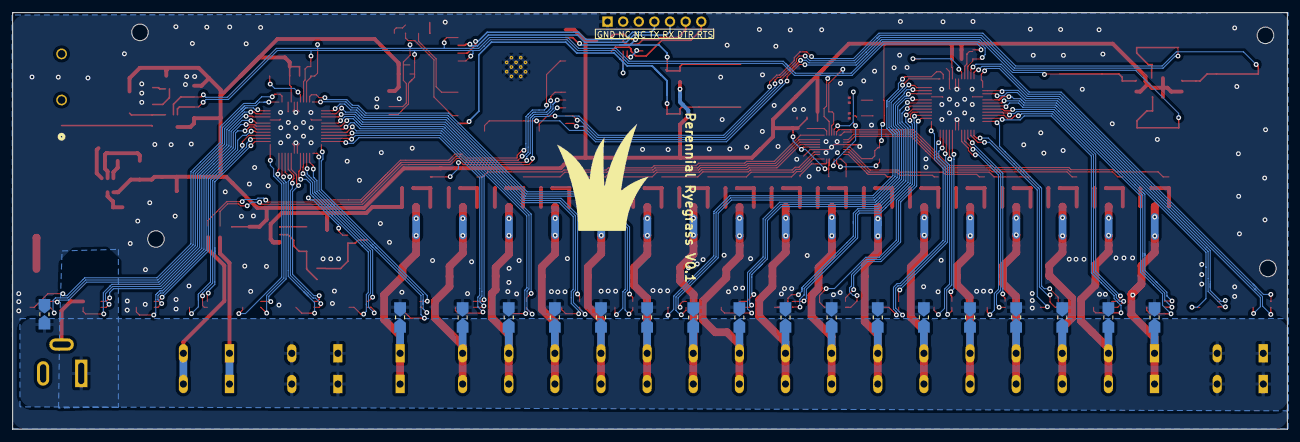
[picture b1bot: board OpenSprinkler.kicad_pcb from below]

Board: 2 copper layers, 207.3 x 67.7 mm, 214 parts (18 on the bottom side), 170 nets.

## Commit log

2025-01-19 Cleaning up junk
2025-01-22 fixing connector
2025-02-17 Updating pcb
